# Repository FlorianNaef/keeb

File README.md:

# keeb

For Kicad to work, you need 
1. The symbols and footprints by [scottokeebs](https://github.com/joe-scotto/scottokeebs/tree/main/Extras/ScottoKicad)
2. The symbols and footprints in this repo. For this you need to set a path to the directory of this repo and add the symbol library and footprints like in 1.

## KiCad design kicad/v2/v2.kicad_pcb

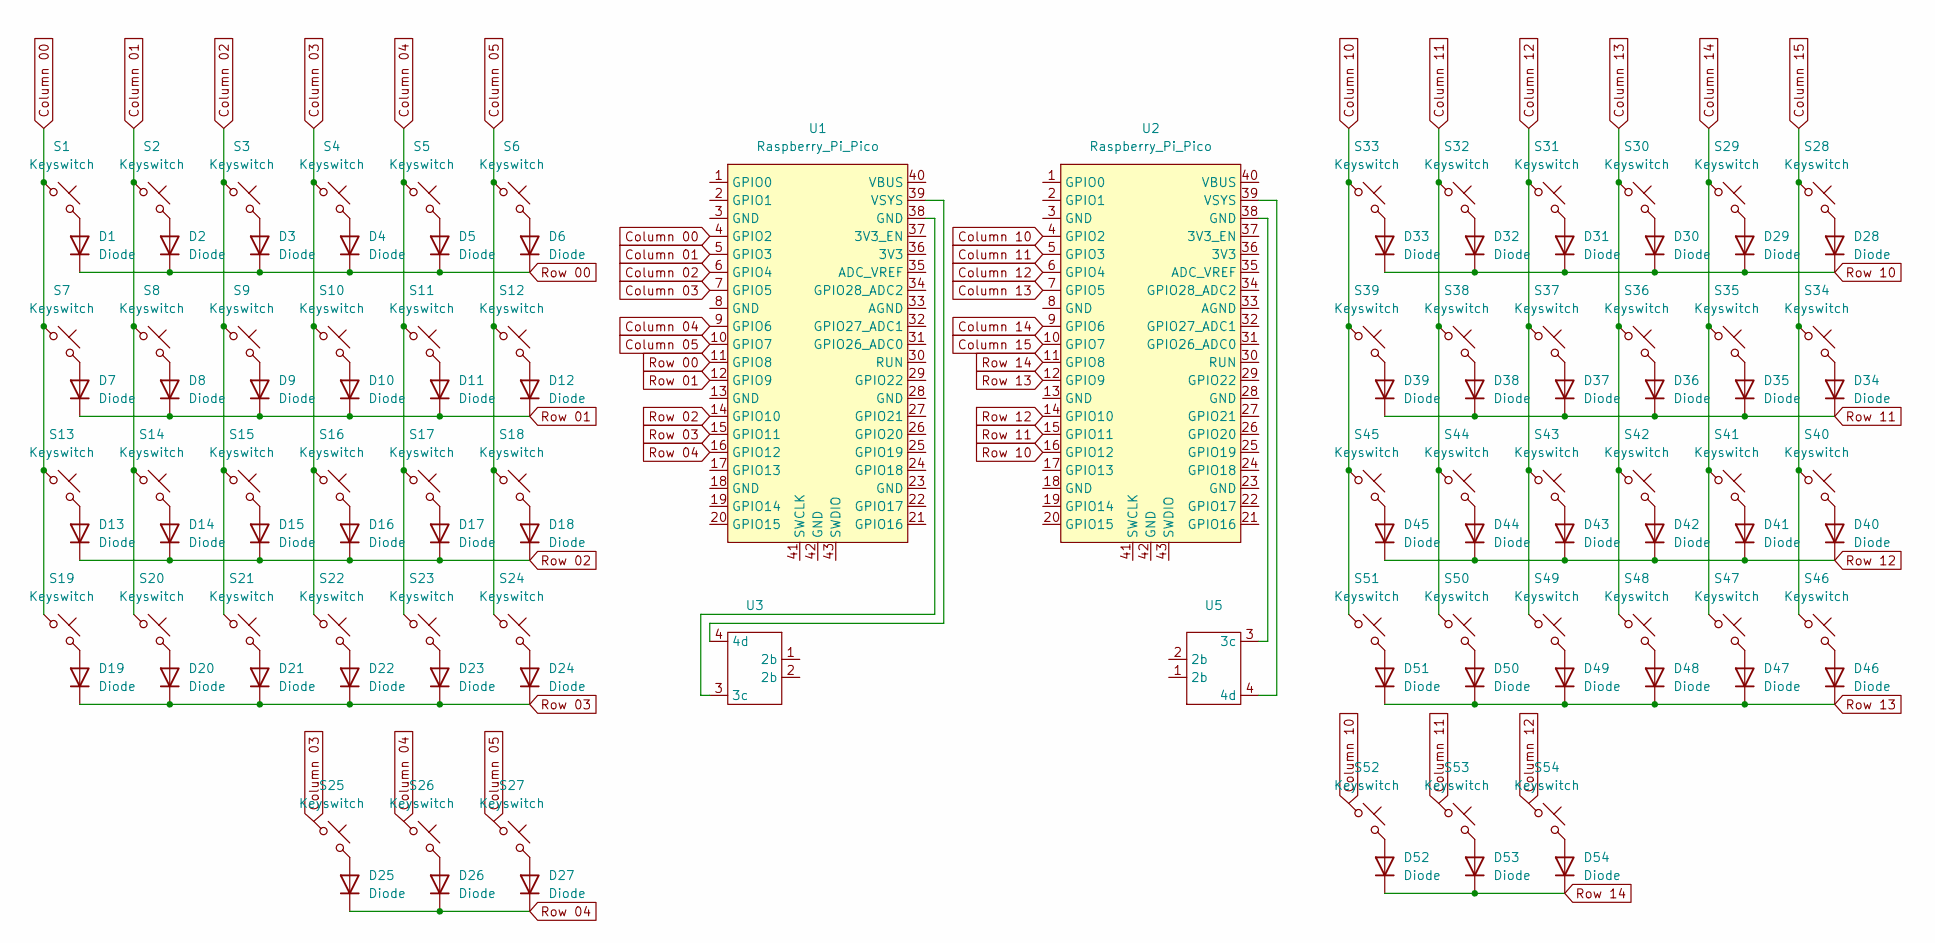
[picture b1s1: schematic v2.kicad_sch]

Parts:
D1, D2, D3, D4, D5, D6, D7, D8, D9, D10, D11, D12, D13, D14, D15, D16, D17, D18, D19, D20, D21, D22, D23, D24, D25, D26, D27, D28, D29, D30, D31, D32, D33, D34, D35, D36, D37, D38, D39, D40, D41, D42, D43, D44, D45, D46, D47, D48, D49, D50, D51, D52, D53, D54: Diode; Diode_DO-35
S1, S2, S3, S4, S5, S6, S7, S8, S9, S10, S11, S12, S13, S14, S15, S16, S17, S18, S19, S20, S21, S22, S23, S24, S25, S26, S27, S28, S29, S30, S31, S32, S33, S34, S35, S36, S37, S38, S39, S40, S41, S42, S43, S44, S45, S46, S47, S48, S49, S50, S51, S52, S53, S54: Keyswitch; Choc_V1_1.00u
U1, U2: Raspberry_Pi_Pico
U3, U5: Lumberg 1503 29 Klinken-Einbaubuchse

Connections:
Column 00: S1.1, S7.1, S13.1, S19.1, U1.4 (GPIO2)
Column 01: S2.1, S8.1, S14.1, S20.1, U1.5 (GPIO3)
Column 02: S3.1, S9.1, S15.1, S21.1, U1.6 (GPIO4)
Column 03: S4.1, S10.1, S16.1, S22.1, S25.1, U1.7 (GPIO5)
Column 04: S5.1, S11.1, S17.1, S23.1, S26.1, U1.9 (GPIO6)
Column 05: S6.1, S12.1, S18.1, S24.1, S27.1, U1.10 (GPIO7)
Column 10: S33.1, S39.1, S45.1, S51.1, S52.1, U2.4 (GPIO2)
Column 11: S32.1, S38.1, S44.1, S50.1, S53.1, U2.5 (GPIO3)
Column 12: S31.1, S37.1, S43.1, S49.1, S54.1, U2.6 (GPIO4)
Column 13: S30.1, S36.1, S42.1, S48.1, U2.7 (GPIO5)
Column 14: S29.1, S35.1, S41.1, S47.1, U2.9 (GPIO6)
Column 15: S28.1, S34.1, S40.1, S46.1, U2.10 (GPIO7)
unnamed: D1.2 (A), S1.2
unnamed: D2.2 (A), S2.2
unnamed: D3.2 (A), S3.2
unnamed: D4.2 (A), S4.2
unnamed: D5.2 (A), S5.2
unnamed: D6.2 (A), S6.2
unnamed: D7.2 (A), S7.2
unnamed: D8.2 (A), S8.2
unnamed: D9.2 (A), S9.2
unnamed: D10.2 (A), S10.2
unnamed: D11.2 (A), S11.2
unnamed: D12.2 (A), S12.2
unnamed: D13.2 (A), S13.2
unnamed: D14.2 (A), S14.2
unnamed: D15.2 (A), S15.2
unnamed: D16.2 (A), S16.2
unnamed: D17.2 (A), S17.2
unnamed: D18.2 (A), S18.2
unnamed: D19.2 (A), S19.2
unnamed: D20.2 (A), S20.2
unnamed: D21.2 (A), S21.2
unnamed: D22.2 (A), S22.2
unnamed: D23.2 (A), S23.2
unnamed: D24.2 (A), S24.2
unnamed: D25.2 (A), S25.2
unnamed: D26.2 (A), S26.2
unnamed: D27.2 (A), S27.2
unnamed: D28.2 (A), S28.2
unnamed: D29.2 (A), S29.2
unnamed: D30.2 (A), S30.2
unnamed: D31.2 (A), S31.2
unnamed: D32.2 (A), S32.2
unnamed: D33.2 (A), S33.2
unnamed: D34.2 (A), S34.2
unnamed: D35.2 (A), S35.2
unnamed: D36.2 (A), S36.2
unnamed: D37.2 (A), S37.2
unnamed: D38.2 (A), S38.2
unnamed: D39.2 (A), S39.2
unnamed: D40.2 (A), S40.2
unnamed: D41.2 (A), S41.2
unnamed: D42.2 (A), S42.2
unnamed: D43.2 (A), S43.2
unnamed: D44.2 (A), S44.2
unnamed: D45.2 (A), S45.2
unnamed: D46.2 (A), S46.2
unnamed: D47.2 (A), S47.2
unnamed: D48.2 (A), S48.2
unnamed: D49.2 (A), S49.2
unnamed: D50.2 (A), S50.2
unnamed: D51.2 (A), S51.2
unnamed: D52.2 (A), S52.2
unnamed: D53.2 (A), S53.2
unnamed: D54.2 (A), S54.2
unnamed: U1.39 (VSYS), U3.4 (4d)
unnamed: U2.39 (VSYS), U5.4 (4d)
unnamed: U1.38 (GND), U3.3 (3c)
unnamed: U2.38 (GND), U5.3 (3c)
Row 00: D1.1 (K), D2.1 (K), D3.1 (K), D4.1 (K), D5.1 (K), D6.1 (K), U1.11 (GPIO8)
Row 01: D7.1 (K), D8.1 (K), D9.1 (K), D10.1 (K), D11.1 (K), D12.1 (K), U1.12 (GPIO9)
Row 02: D13.1 (K), D14.1 (K), D15.1 (K), D16.1 (K), D17.1 (K), D18.1 (K), U1.14 (GPIO10)
Row 03: D19.1 (K), D20.1 (K), D21.1 (K), D22.1 (K), D23.1 (K), D24.1 (K), U1.15 (GPIO11)
Row 04: D25.1 (K), D26.1 (K), D27.1 (K), U1.16 (GPIO12)
Row 10: D28.1 (K), D29.1 (K), D30.1 (K), D31.1 (K), D32.1 (K), D33.1 (K), U2.16 (GPIO12)
Row 11: D34.1 (K), D35.1 (K), D36.1 (K), D37.1 (K), D38.1 (K), D39.1 (K), U2.15 (GPIO11)
Row 12: D40.1 (K), D41.1 (K), D42.1 (K), D43.1 (K), D44.1 (K), D45.1 (K), U2.14 (GPIO10)
Row 13: D46.1 (K), D47.1 (K), D48.1 (K), D49.1 (K), D50.1 (K), D51.1 (K), U2.12 (GPIO9)
Row 14: D52.1 (K), D53.1 (K), D54.1 (K), U2.11 (GPIO8)

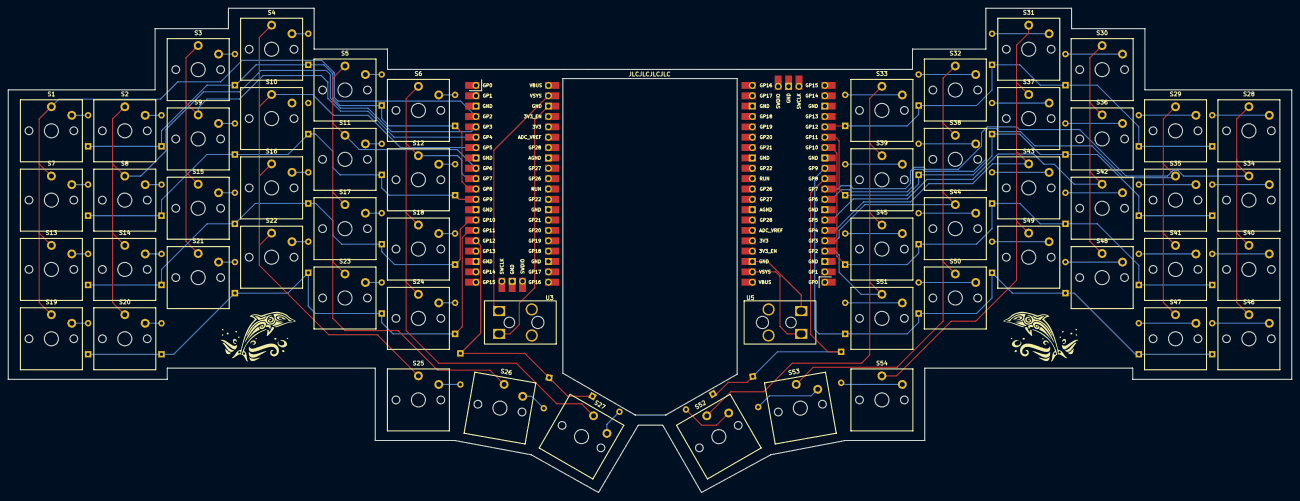
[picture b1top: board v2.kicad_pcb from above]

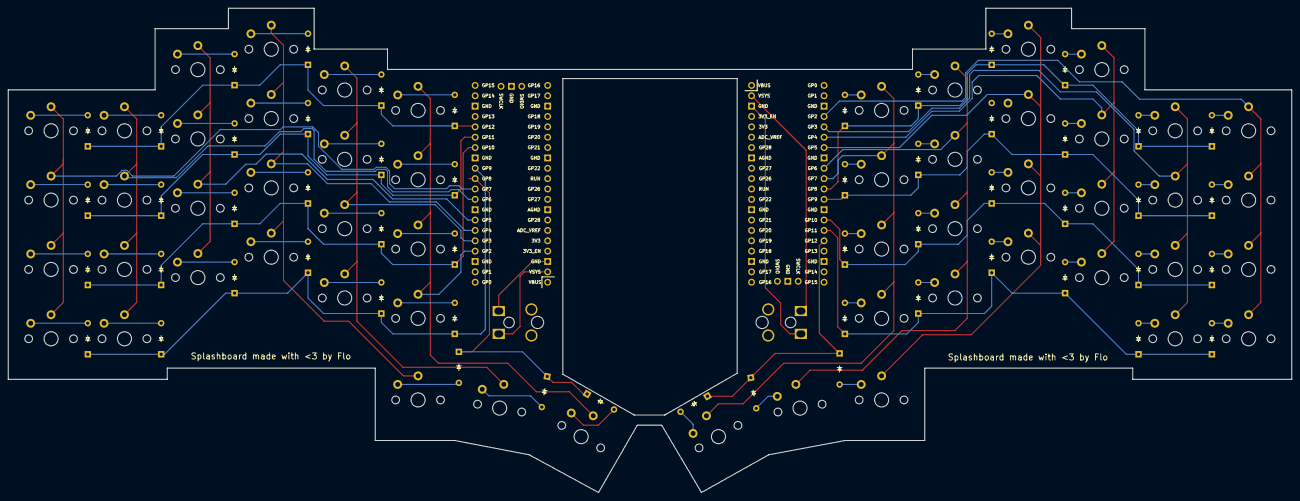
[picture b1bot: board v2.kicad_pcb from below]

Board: 2 copper layers, 314.8 x 118.8 mm, 112 parts (54 on the bottom side), 80 nets.

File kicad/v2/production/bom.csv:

Designator,Footprint,Quantity,Value,LCSC Part #
"D1, D10, D11, D12, D13, D14, D15, D16, D17, D18, D19, D2, D20, D21, D22, D23, D24, D25, D26, D27, D28, D29, D3, D30, D31, D32, D33, D34, D35, D36, D37, D38, D39, D4, D40, D41, D42, D43, D44, D45, D46, D47, D48, D49, D5, D50, D51, D52, D53, D54, D6, D7, D8, D9",Diode_DO-35,54,Diode,
"S1, S10, S11, S12, S13, S14, S15, S16, S17, S18, S19, S2, S20, S21, S22, S23, S24, S25, S26, S27, S28, S29, S3, S30, S31, S32, S33, S34, S35, S36, S37, S38, S39, S4, S40, S41, S42, S43, S44, S45, S46, S47, S48, S49, S5, S50, S51, S52, S53, S54, S6, S7, S8, S9",Choc_V1_1.00u,54,Keyswitch,
"U1, U2",Raspberry_Pi_Pico,2,Raspberry_Pi_Pico,
"U3, U5",Lumberg 1503 29 Klinken-Einbaubuchse,2,~,

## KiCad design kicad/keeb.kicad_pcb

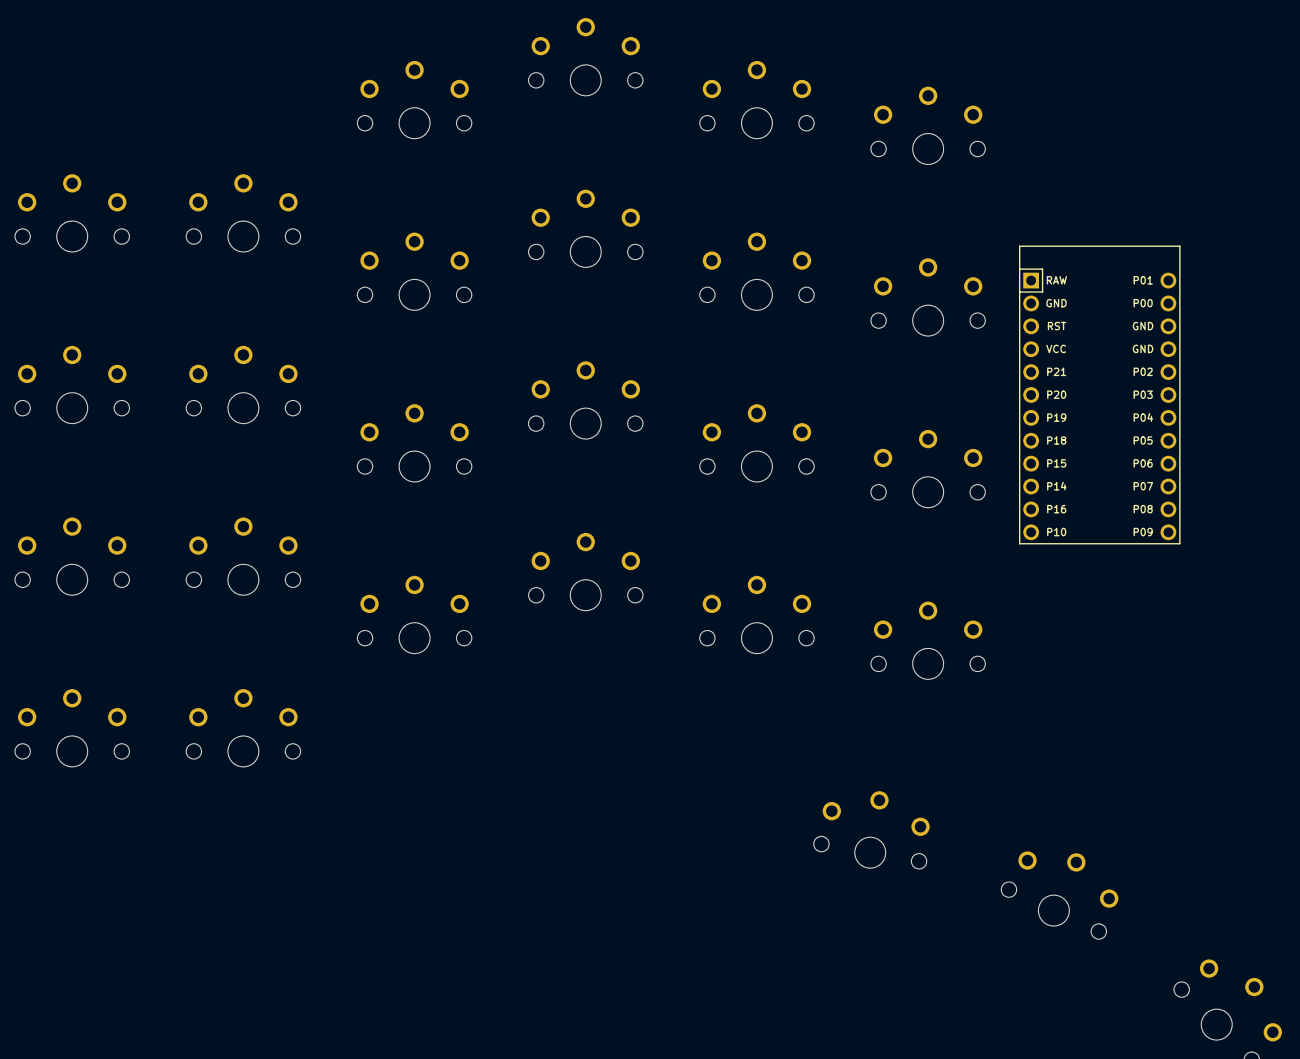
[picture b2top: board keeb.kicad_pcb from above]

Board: 2 copper layers, 28 parts (0 on the bottom side), 18 nets, no tracks yet.

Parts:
MCU1: ProMicro
S1, S2, S3, S4, S5, S6, S7, S8, S9, S10, S11, S12, S13, S14, S15, S16, S17, S18, S19, S20, S21, S22, S23, S24, S25, S26, S27: PG1350

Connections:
GND: MCU1.2, MCU1.15, MCU1.16, S1.1, S2.1, S3.1, S4.1, S5.1, S6.1, S7.1, S8.1, S9.1, S10.1, S11.1, S12.1, S13.1, S14.1, S15.1, S16.1, S17.1, S18.1, S19.1, S20.1, S21.1, S22.1, S23.1, S24.1, S25.1, S26.1, S27.1
matrix_index_bottom: MCU1.20, S17.2
matrix_index_home: MCU1.12, S18.2
matrix_index_top: MCU1.6, S19.2
matrix_inner_bottom: MCU1.21, S21.2
matrix_inner_home: MCU1.13, S22.2
matrix_inner_top: MCU1.5, S23.2
matrix_middle_bottom: MCU1.19, S13.2
matrix_middle_home: MCU1.11, S14.2
matrix_middle_top: MCU1.7, S15.2
matrix_pinky_bottom: MCU1.17, S5.2
matrix_pinky_home: MCU1.9, S6.2
matrix_pinky_top: MCU1.22, S7.2
matrix_ring_bottom: MCU1.18, S9.2
matrix_ring_home: MCU1.10, S10.2
matrix_ring_top: MCU1.8, S11.2
thumb_reachy: MCU1.24, S26.2
thumb_tucky: MCU1.23, S25.2

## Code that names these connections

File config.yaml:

points:
  zones:
    matrix:
      columns:
        outer:
        pinky:
        ring.key.stagger: 0.66U
        middle.key.stagger: 0.25U
        index.key.stagger: -0.25U
        inner.key.stagger: -0.15U
      rows:
        bottom.padding: U
        home.padding: U
        top.padding: U
        numbers.padding: U
    thumb:
      anchor:
        ref: matrix_index_bottom
        shift: [0.66U, -1.25U]
        rotate: -10
      columns:
        tucky:
          key.name: thumb_tucky
        reachy:
          key.spread: U
          key.splay: -15
          key.origin: [-0.5U, -0.5U]
          key.name: thumb_reachy
        reacher:
          key.spread: U
          key.splay: -20
          key.origin: [-0.5U,-0.5U]
          key.name: thumb_reacher

pcbs:
  simple_split:
    footprints:
      keys:
        what: choc # TODO: Check
        where: true
        params:
          from: GND
          to: "{{name}}"
          reverse: true
          keycaps: true
      mcu:
        what: promicro
        where:
          - ref: matrix_inner_home
            shift: [1U, 0.5U]
            rotate: -90
        params:
          P7: matrix_pinky_top
          P18: matrix_ring_top
          P19: matrix_middle_top
          P20: matrix_index_top
          P21: matrix_inner_top
          P15: matrix_pinky_home
          P14: matrix_ring_home
          P16: matrix_middle_home
          P10: matrix_index_home
          P1: matrix_inner_home
          P2: matrix_pinky_bottom
          P3: matrix_ring_bottom
          P4: matrix_middle_bottom
          P5: matrix_index_bottom
          P6: matrix_inner_bottom
          P8: thumb_tucky
          P9: thumb_reachy

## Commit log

2024-11-19 add: basic ergogen config
2024-11-19 add: number row
2024-11-20 add: outline
2024-11-22 add: kicad project
2024-11-22 refactor: move config
2024-11-22 remove: outlines
2024-12-08 add: v1 4x4 matrix
2024-12-09 add: sheriff-config by ajgamma
2024-12-09 add: v2
2024-12-22 fix: symetry
2024-12-30 add: 3.5mm jacks with very messy wiring
2025-01-01 add: finishing touches
2025-01-01 fix: make pcb pass dfm check
2025-01-01 add: second stability beam
2025-01-30 add qmk
2025-01-30 add full qmk
2025-01-31 add minor keymap changes
2025-02-01 add gitignore
2025-02-01 add half duplex and new keymap
2025-02-10 add: save script
2025-02-15 add: finalized keymap
2025-02-15 fix: save script
